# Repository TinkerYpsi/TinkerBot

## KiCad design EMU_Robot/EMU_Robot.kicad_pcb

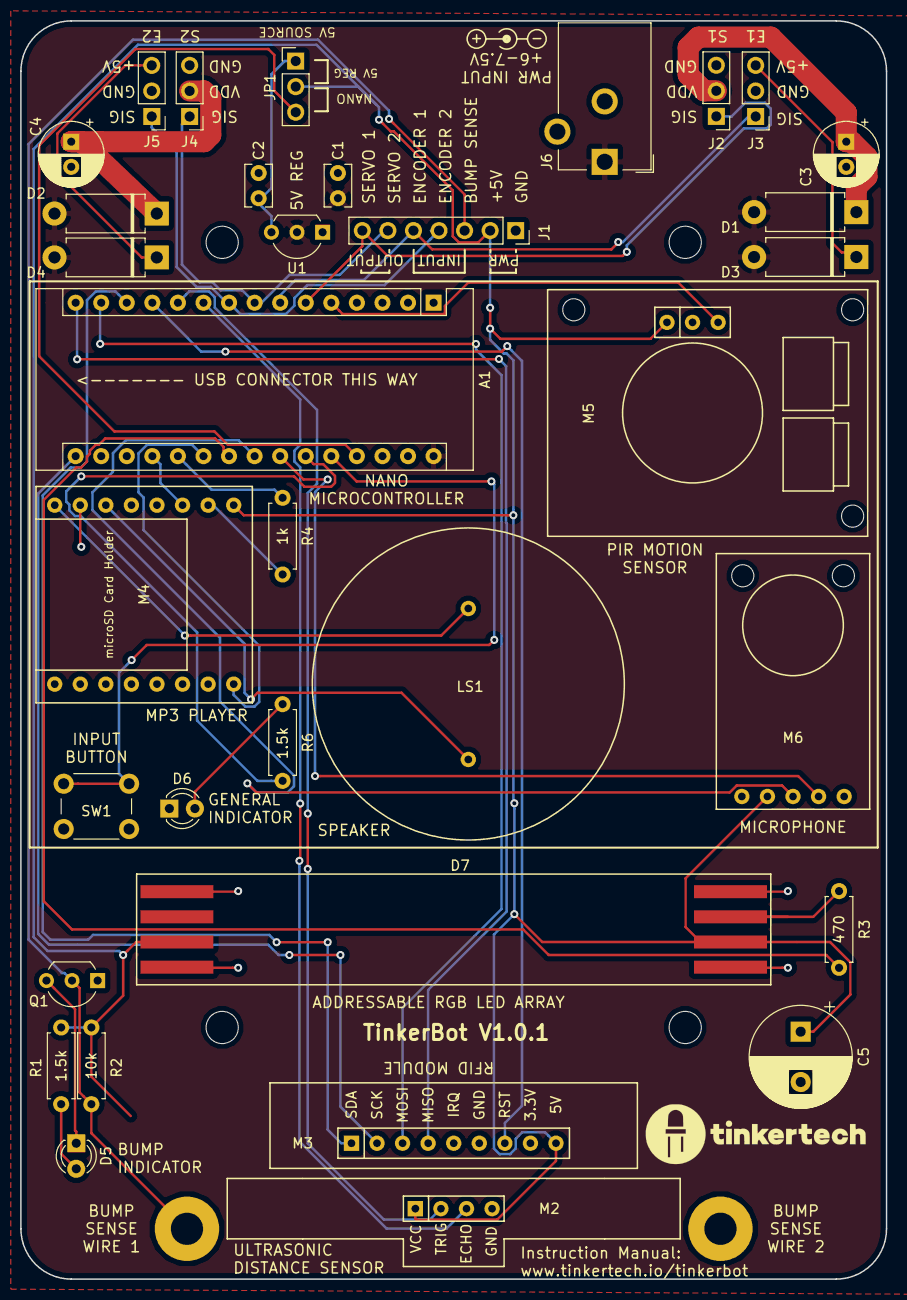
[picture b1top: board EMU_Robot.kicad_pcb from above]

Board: 2 copper layers, 86.0 x 125.0 mm, 48 parts (0 on the bottom side), 37 nets.

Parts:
A1: Arduino_Nano_v3.x; Arduino_Nano
BB1: Breadboard-Mini; BREADBOARD-MINI
C1, C2: 1uF; C_Rect_L4.0mm_W2.5mm_P2.50mm
C3, C4: 470uF; CP_Radial_D6.3mm_P2.50mm
C5: 1000uF; CP_Radial_D10.0mm_P5.00mm
D1, D2, D3, D4: B240AE-13; D_DO-15_P10.16mm_Horizontal
D5, D6: LED; LED_D3.0mm
D7: WS2812S_8Px_Strip; WS2812-8px-Stick-(Hand_Solder)
H1, H1#2, H2, H2#2: MountingHole; MountingHole_3.2mm_M3
H3, H6, H7, H8, H9: MountingHole; MountingHole_2.2mm_M2
H4, H5: MountingHole_Pad; MountingHole_3.2mm_M3_Pad
J1: Conn_01x07_Female; PinSocket_1x07_P2.54mm_Vertical
J2, J3, J4, J5: Conn_01x03_Male; PinHeader_1x03_P2.54mm_Vertical
J6: Barrel_Jack; BarrelJack_CUI_PJ-102AH_Horizontal
JP1: Jumper_3_Bridged12; PinHeader_1x03_P2.54mm_Vertical
LS1: Speaker; Speaker_30mm-Dia_15mm-Pitch
M2: HC-SR04; HC-SR04-Labeled-Short-Silk
M3: RobotDyn_RFID_Module; RobotDyn_RFID_Module-Vert
M4: DFPlayer_Mini
M5: RobotDyn_PIR_Motion_Sensor
M6: MAX9814_Microphone_Module
Q1: 2N3906; TO-92_Inline_Wide
R1: 10k; R_Axial_DIN0207_L6.3mm_D2.5mm_P7.62mm_Horizontal
R2, R6: 1.5k; R_Axial_DIN0207_L6.3mm_D2.5mm_P7.62mm_Horizontal
R3: 470; R_Axial_DIN0207_L6.3mm_D2.5mm_P7.62mm_Horizontal
R4: 1k; R_Axial_DIN0207_L6.3mm_D2.5mm_P7.62mm_Horizontal
SLK1: TT_Logo; TinkerTech-Logo_22.4x6.5mm_SilkScreen
SLK2: Barrel_Polarity; Symbol_Barrel_Polarity
SW1: SW_Push; SW_PUSH_6mm_H4.3mm
U1: MCP1702-5002E_TO92; TO-92L_Inline_Wide

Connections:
+5V: C5.1, D7.3, D7.6, J1.2, JP1.2, M2.1, M3.9, M4.1, M5.1, M6.2, R1.1, R2.1
+5VA: C2.1, JP1.1, U1.3
+5VP: A1.27, JP1.3
BUMP_SENSE: H4.1, J1.3, Q1.2, R1.2
DIN: A1.22, R3.2
ENCODER_1_SIGNAL: A1.7, J1.5, J3.1
ENCODER_2_SIGNAL: A1.9, J1.4, J5.1
GND: A1.4, A1.29, C1.2, C2.2, C3.2, C4.2, C5.2, D6.1, D7.1, D7.4, D7.5, D7.8, H5.1, J1.1, J2.3, J3.2, J4.3, J5.2, J6.2, M2.4, M3.6, M4.7, M4.10, M5.2, M6.1, Q1.1, SW1.2, U1.1
MIC_GAIN: A1.23, M6.3
MIC_OUTPUT: A1.24, M6.4
MISO: A1.15, M3.4
MOSI: A1.14, M3.3
MP3_BUSY: A1.21, M4.16
unnamed: A1.25, R6.1
unnamed: A1.26, SW1.1
unnamed: D3.1, J3.3
unnamed: D4.1, J5.3
unnamed: D5.1, Q1.3
unnamed: D5.2, R2.2
unnamed: D6.2, R6.2
unnamed: D7.7, R3.1
unnamed: LS1.1, M4.8
unnamed: LS1.2, M4.6
unnamed: M4.2, R4.1
PIR_OUTPUT: A1.5, M5.3
RFID_RST: A1.12, M3.7
SCK: A1.16, M3.2
SERVO_1_PWR: C3.1, D1.1, J2.2
SERVO_1_SIGNAL: A1.6, J1.7, J2.1
SERVO_2_PWR: C4.1, D2.1, J4.2
SERVO_2_SIGNAL: A1.8, J1.6, J4.1
SOFT_RX: A1.19, M4.3
SOFT_TX: A1.20, R4.2
SS: A1.13, M3.1
US_ECHO: A1.10, M2.3
US_TRIG: A1.11, M2.2
VDD: A1.30, C1.1, D1.2, D2.2, D3.2, D4.2, J6.1, U1.2

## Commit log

2019-09-05 :tada: Added .gitattributes & .gitignore files
